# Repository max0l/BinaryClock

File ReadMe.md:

# BinaryClock

## This Project creates a nice Binary Clock using the Atmega48a, some 3D Printing, a DCF77, and as well a CNC-Machine

We startet working on this duo a Assignment from our Uni

If you have any questions, you can create an Issue

Here are two videos showing the result:

Final Binary Clock Showcase: https://www.youtube.com/watch?v=2T8O-BEcYGA

DCF77 Showcase: https://youtube.com/shorts/U24RXPAsWoY

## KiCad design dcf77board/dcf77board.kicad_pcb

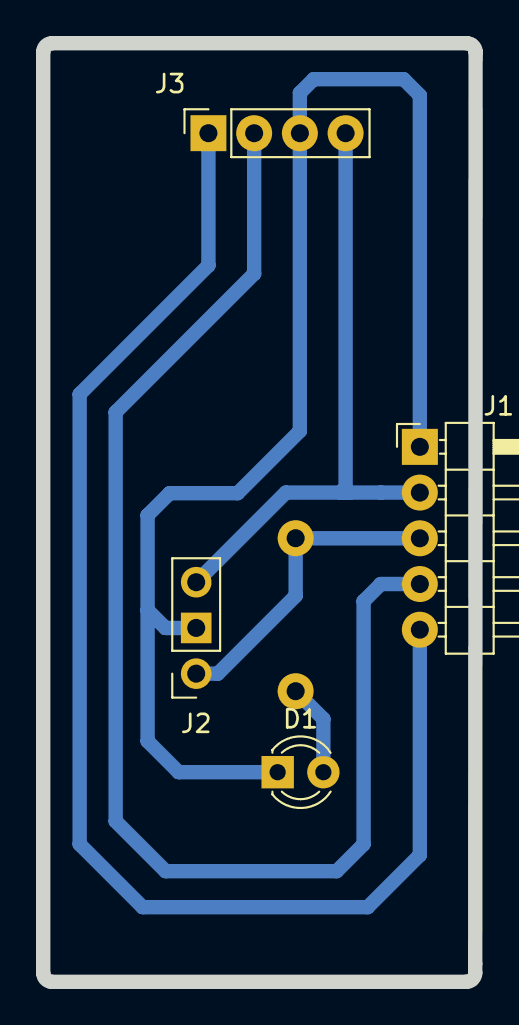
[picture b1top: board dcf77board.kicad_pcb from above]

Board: 2 copper layers, 24.0 x 52.1 mm, 4 parts (0 on the bottom side), 5 nets.

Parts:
D1: LED; LED_D3.0mm
J1: Connector to Mainboard; PinHeader_1x05_P2.54mm_Horizontal
J2: extern power; PinSocket_1x03_P2.54mm_Vertical
J3: Connector to which the DCF77 gets solderd on; PinSocket_1x04_P2.54mm_Vertical

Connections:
/3V: J1.2, J2.3, J3.4
/Ground: D1.1 (K), J1.1, J2.2, J3.3
/dcf77Data: J1.4, J3.2
/dcf77Enable: J1.5, J3.1
/debug: D1.2 (A), J1.3, J2.1

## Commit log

2024-01-06 LED Config done
2024-01-07 First Steps, Interrupts kinda working, but not really
2024-01-07 Interrupt working fine
2024-01-09 Timer0 working, now on Quartz timer
2024-03-06 ´creating new Toolchain to avoid Microchip Studio
2024-03-06 added gitignore and removed non important files for VSC
2024-03-07 changed some interrupt values
2024-03-07 timer is correct now
2024-03-12 Timer is going now and time is displayed
2024-03-12 implemented sleep mode and thought about power saving
2024-03-13 Update main.c
    Button 2, 3
    Set time
    Brightnesslvl
    pwm brightnesslvl not inclouded how to?
2024-03-13 small changes
2024-03-17 Implementing DCF77, but reading is difficult since ICP is somewhere else and need to do this in software
2024-03-19 somehow working, needs a lot of cleaning and bug fixes
2024-03-19 some cleanup, maybe needs bug fixes
2024-03-20 interpretation works, but does not work right
2024-03-20 fixed some bugs
2024-03-20 all issues fixed?
2024-03-24 added a return if there is no signal from the dcf77 for 5 seconds
2024-03-26 test
2024-03-26 set to 0 when no signal has been received
2024-03-26 Implemented buttons. Prellen needs to be fixed
2024-03-26 Fixed make issues after merge
2024-03-26 Made some improvements: removed unnecessary extern declarations switched to pragma once
2024-03-26 Added Drift negation and put initDcf7() before initialising the buttons. Also changed debug bin to PD5
2024-03-27 fixing some stuff regarding the drift and enabled debugging output on the dcf77 module
2024-03-27 fixed a bug where dcf77 enabled pin was disabled whole time and added a trycounter to dcf77 so it will stop trying to read the signal after 3 tries
2024-03-27 added more power saving options (power.h) and other error handling in dcf77
2024-03-27 bug fixes. Buttons Working
2024-03-27 reanabled dcf77 module
2024-03-27 a little cleanup, needs final test
2024-03-27 removed comments
2024-03-27 some imptovements. One fix regarding the dcf 77 signal: tryCounter
2024-03-27 fixed typo in dcf77.c
2024-03-28 imporved power saving and reduced polling
2024-03-28 improved error handling on dcf77 module: errors are cleared after one try and signalOk will check if digit is had come to 36+
2024-03-28 Added other files like the KiCad project files and the case STL file new file: ReadMe.md new file: case/binaryClock Case v6.stl new file: dcf77board/dcf77board.kicad_pcb new file: dcf77board/dcf77boa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
